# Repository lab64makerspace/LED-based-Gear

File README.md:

# LED-based-Gear
*Equipment to help study the optical control of protein function*

This repo contains the material to produce and use the devices used in the [Cui Lab](https://cuilab.stanford.edu) at Stanford for studying the optical control of protein function. You can learn more about their work [here](https://cuilab.stanford.edu/optical-control-protein-function) but briefly-

### Optical Control of Protein Function

Cells constantly process environmental cues, such as growth factors, to make decisions on cell fate, e.g. survival, proliferation, differentiation, migration, and apoptosis. To ensure proper conversion of a specific environmental input into a distinct cellular output, the activation of intracellular signaling pathways is tightly regulated in space and time.

Compared with our understanding of the roles various proteins play in a multitude of cellular signaling pathways, much less is understood about how these temporal and spatial aspects affect cell behavior, largely due to the lack of effective tools to precisely regulate signaling pathways in space and time.

Our approach is to use light-gated protein-protein interaction systems to control the activation and inactivation of intracellular signaling pathways. This ability to optically control signaling pathways offers unprecedented precision in temporal and spatial dimensions.

### Devices to provide controlled illumination

Controllable illumination sources are required to work in conjuntion with the molecular tools used in the Cui Lab. Specifically, a light source with tunable intensity and on/off durations is desired for spatiotemporal control of the activation of these molecular tools in cells. Simple light sources are readily made using electronic prototyping techniques but there is a desire to gain more precise control of the illumination, so we (folks in lab64) have been helping produce the equipment described here.

### About lab64
[lab64](https://lab64.stanford.edu) is an electronics and systems makerspace located in the David Packard Electrical Engineering Building at Stanford. Occasionally we have the privilege of helping to build equipment to support some of the exciting research projects here on campus. This is one of those projects!

#### Questions or comments
If you have questions about the hardware, firmware, or software described here, please send Steve Clark a note at steven DOT clark AT stanford DOT edu

If you have questions about the research, molecular tools, etc. please contact Professor Cui by sending a note to bcui AT stanford DOT edu

Thank you for your interest!

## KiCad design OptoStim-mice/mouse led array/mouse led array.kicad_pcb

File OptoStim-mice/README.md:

# OptoStim-mice

This device facilitates the optical stimulation of light-gated molecular interaction systems in mice and allows for the uniform illumination (450 nm) of mouse subjects as they move during exposure.

### Description of device

This is a 7x7 array of high power LEDs (SST-10-B-B130-N450) connected in parallel-series (sets of 7) in a grid with 15mm spacing between the LEDs with a simple on/off as supplied by an external power source. The device draws 21V and 2.45A, although the intensity of the LEDs may be tuned by varying the power.

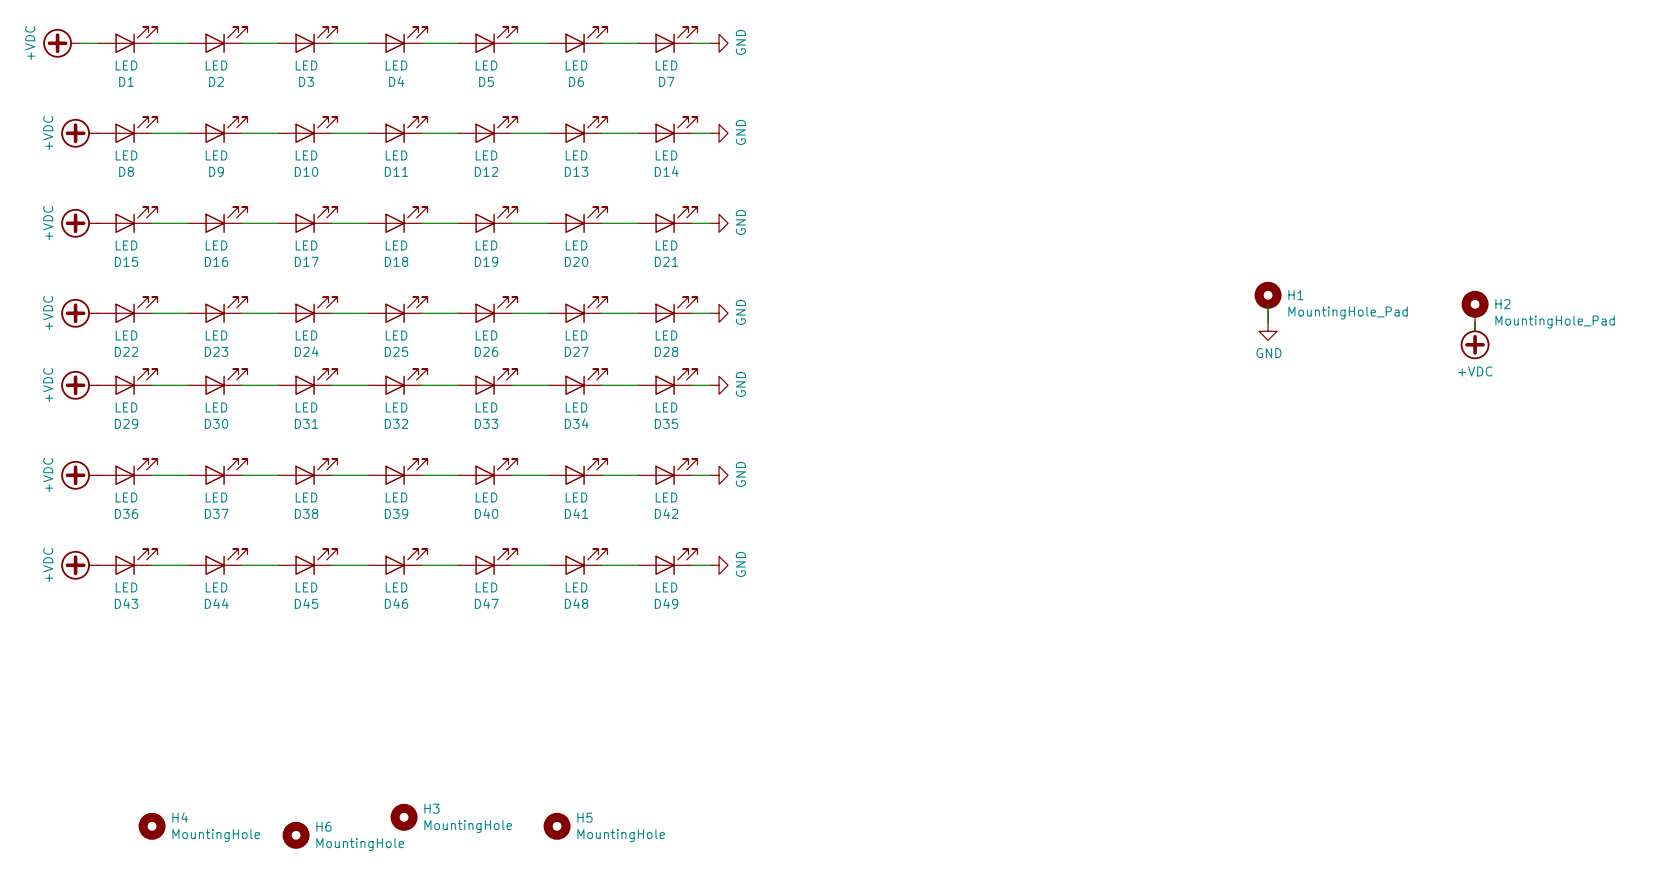
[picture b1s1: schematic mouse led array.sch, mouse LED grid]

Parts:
D1, D2, D3, D4, D5, D6, D7, D8, D9, D10, D11, D12, D13, D14, D15, D16, D17, D18, D19, D20, D21, D22, D23, D24, D25, D26, D27, D28, D29, D30, D31, D32, D33, D34, D35, D36, D37, D38, D39, D40, D41, D42, D43, D44, D45, D46, D47, D48, D49: LED; SST-10-B-B130-N450
H1, H2: MountingHole_Pad; z_MountPTH_3mm
H3, H4, H5, H6: MountingHole; MountingHole_5mm

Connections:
+VDC: D1.2 (A), D8.2 (A), D15.2 (A), D22.2 (A), D29.2 (A), D36.2 (A), D43.2 (A), H2.1
GND: D7.1 (K), D14.1 (K), D21.1 (K), D28.1 (K), D35.1 (K), D42.1 (K), D49.1 (K), H1.1
unnamed: D1.1 (K), D2.2 (A)
unnamed: D2.1 (K), D3.2 (A)
unnamed: D3.1 (K), D4.2 (A)
unnamed: D4.1 (K), D5.2 (A)
unnamed: D5.1 (K), D6.2 (A)
unnamed: D6.1 (K), D7.2 (A)
unnamed: D8.1 (K), D9.2 (A)
unnamed: D10.1 (K), D11.2 (A)
unnamed: D9.1 (K), D10.2 (A)
unnamed: D11.1 (K), D12.2 (A)
unnamed: D12.1 (K), D13.2 (A)
unnamed: D13.1 (K), D14.2 (A)
unnamed: D15.1 (K), D16.2 (A)
unnamed: D16.1 (K), D17.2 (A)
unnamed: D17.1 (K), D18.2 (A)
unnamed: D18.1 (K), D19.2 (A)
unnamed: D19.1 (K), D20.2 (A)
unnamed: D20.1 (K), D21.2 (A)
unnamed: D22.1 (K), D23.2 (A)
unnamed: D23.1 (K), D24.2 (A)
unnamed: D24.1 (K), D25.2 (A)
unnamed: D25.1 (K), D26.2 (A)
unnamed: D26.1 (K), D27.2 (A)
unnamed: D27.1 (K), D28.2 (A)
unnamed: D29.1 (K), D30.2 (A)
unnamed: D30.1 (K), D31.2 (A)
unnamed: D31.1 (K), D32.2 (A)
unnamed: D32.1 (K), D33.2 (A)
unnamed: D33.1 (K), D34.2 (A)
unnamed: D34.1 (K), D35.2 (A)
unnamed: D36.1 (K), D37.2 (A)
unnamed: D37.1 (K), D38.2 (A)
unnamed: D38.1 (K), D39.2 (A)
unnamed: D39.1 (K), D40.2 (A)
unnamed: D40.1 (K), D41.2 (A)
unnamed: D41.1 (K), D42.2 (A)
unnamed: D43.1 (K), D44.2 (A)
unnamed: D44.1 (K), D45.2 (A)
unnamed: D45.1 (K), D46.2 (A)
unnamed: D46.1 (K), D47.2 (A)
unnamed: D47.1 (K), D48.2 (A)
unnamed: D48.1 (K), D49.2 (A)

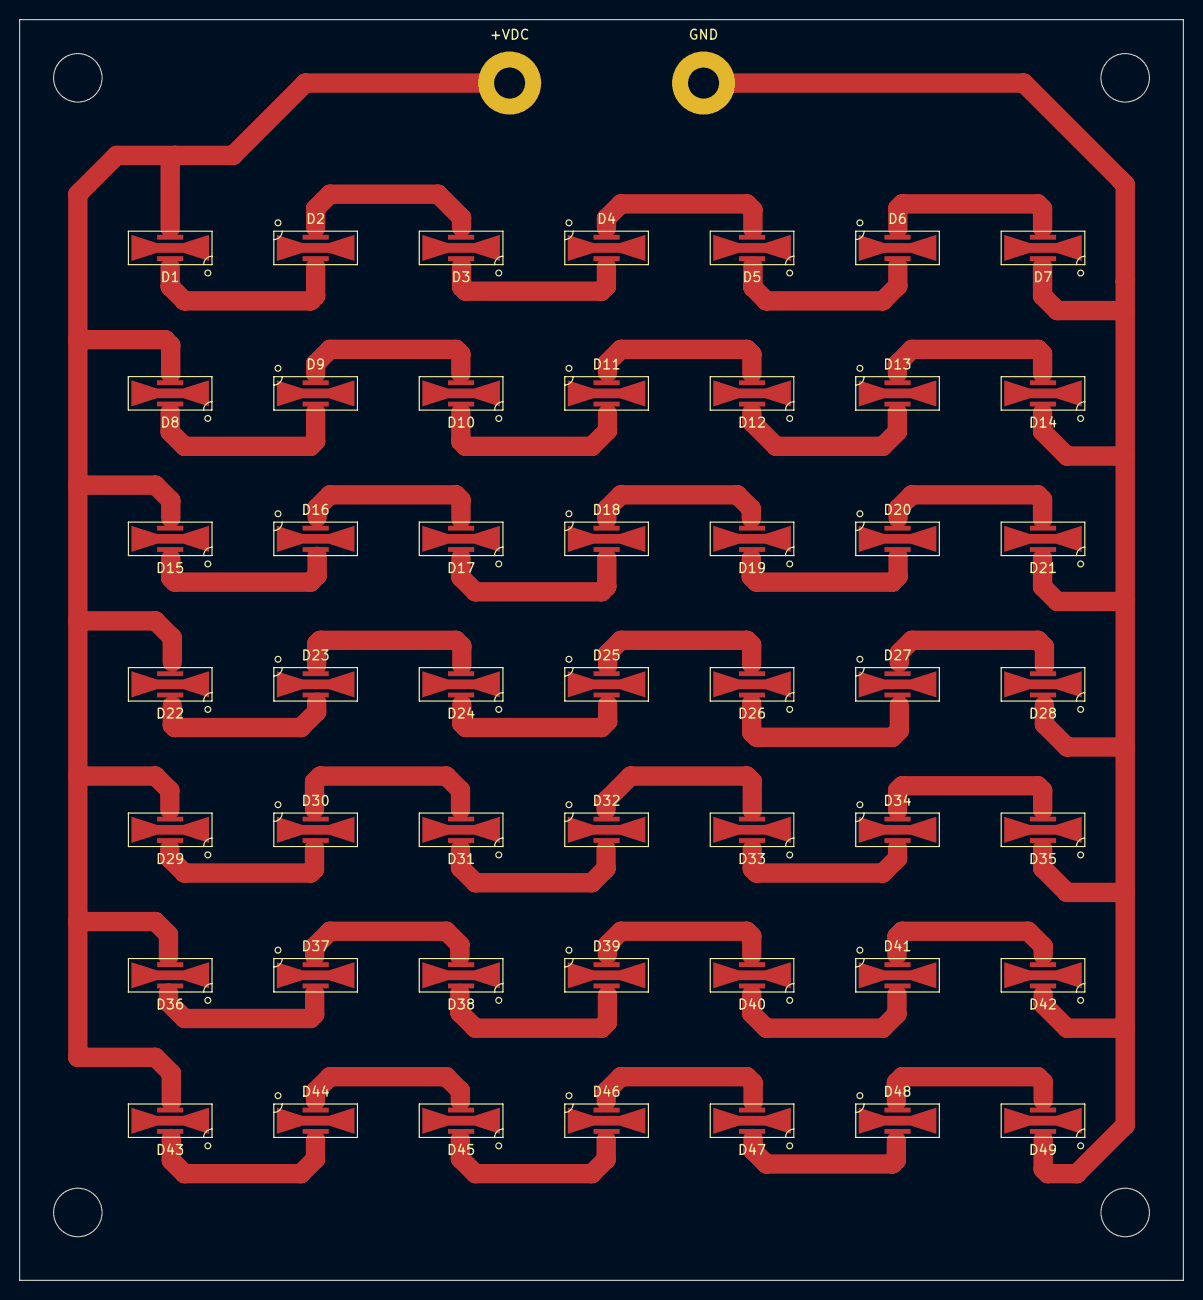
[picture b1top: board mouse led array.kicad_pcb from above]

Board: 2 copper layers, 120.0 x 130.0 mm, 55 parts (0 on the bottom side), 44 nets.

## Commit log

2020-03-18 Create 12-well_plate_light _box
2020-03-18 Create stuff
2020-03-19 Updated main readme
    Test commit with updates to the readme
2020-03-19 updated optostim-mice
    uploaded files for simple mouse LED board design
2020-03-19 Updated README.md in OptoStim-mice
    what is says on the tin
2020-03-30 added single well
2020-03-30 added shift register controls
